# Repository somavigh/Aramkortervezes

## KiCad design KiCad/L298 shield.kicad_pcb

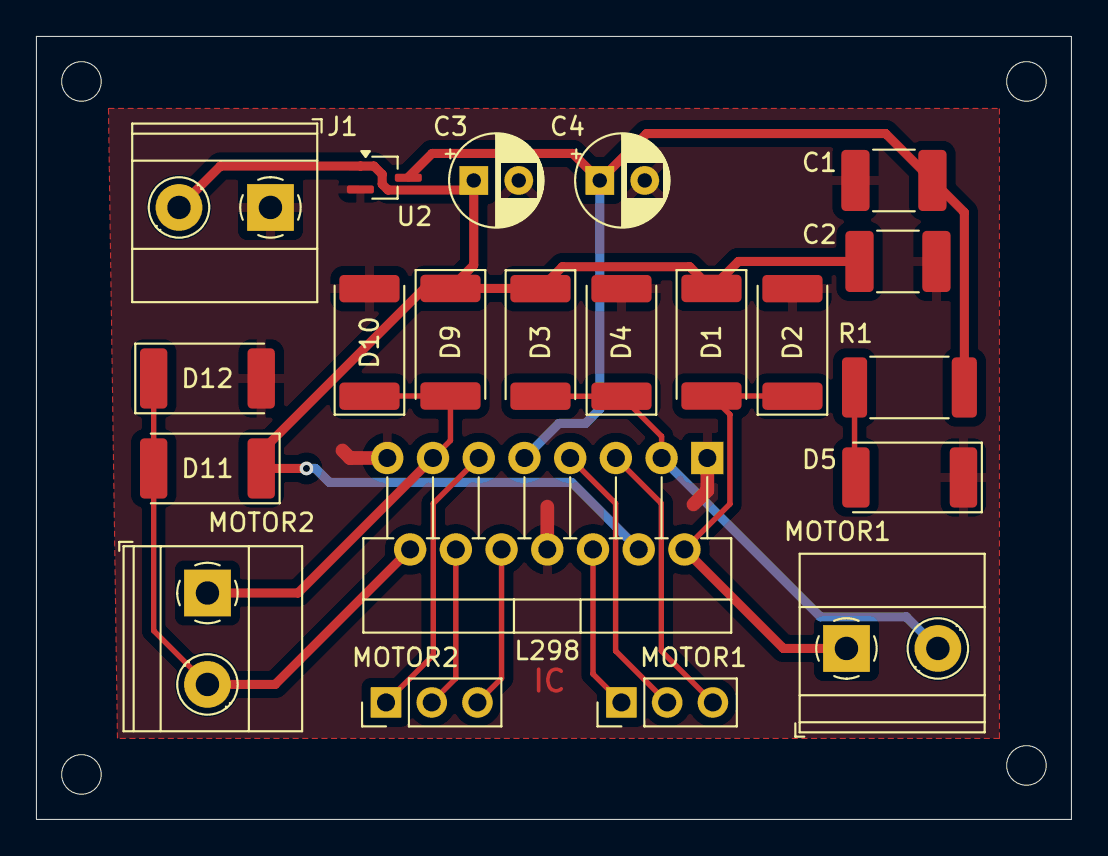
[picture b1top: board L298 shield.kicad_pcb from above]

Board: 2 copper layers, 57.5 x 43.5 mm, 21 parts (0 on the bottom side), 14 nets.

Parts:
C1, C2: 100nF; C_1812_4532Metric_Pad1.57x3.40mm_HandSolder
C3, C4: 47u; CP_Radial_D5.0mm_P2.50mm
D1, D2, D3, D4, D9, D10, D11, D12: 1N4007; D_2512_6332Metric_Pad1.52x3.35mm_HandSolder
D5: LED; LED_2512_6332Metric_Pad1.52x3.35mm_HandSolder
J1: POWER; TerminalBlock_Phoenix_MKDS-1,5-2-5.08_1x02_P5.08mm_Horizont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
L298: L298N; TO-220-15_P2.54x2.54mm_StaggerOdd_Lead4.58mm_Vertical
MOTOR1: MOTOR1 IN; PinHeader_1x03_P2.54mm_Vertical
MOTOR1#2: MOTOR1 OUT; TerminalBlock_Phoenix_MKDS-1,5-2-5.08_1x02_P5.08mm_Horizont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
MOTOR2: MOTOR2 IN; PinHeader_1x03_P2.54mm_Vertical
MOTOR2#2: MOTOR2 OUT; TerminalBlock_Phoenix_MKDS-1,5-2-5.08_1x02_P5.08mm_Horizont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
R1: R; R_2512_6332Metric_Pad1.40x3.35mm_HandSolder
U2: L7805; SOT-323_SC-70_Handsoldering

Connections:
+5V: C1.2, C4.1, L298.9 (Vss), R1.1, U2.3 (OUT)
+12V: C2.1, C3.1, D1.1 (K), D3.1 (K), D9.1 (K), D11.1 (K), J1.2, L298.4 (Vs), U2.1 (IN)
GND: C1.1, C2.2, C3.2, C4.2, D2.2 (A), D4.2 (A), D5.1 (K), D10.2 (A), D12.2 (A), J1.1, L298.1 (SENSE_A), L298.8 (GND), L298.15 (SENSE_B), U2.2 (GND)
unnamed: D1.2 (A), D2.1 (K), L298.2 (OUT1), MOTOR1#2.1
unnamed: D3.2 (A), D4.1 (K), L298.3 (OUT2), MOTOR1#2.2
unnamed: D5.2 (A), R1.2
unnamed: D9.2 (A), D10.1 (K), L298.13 (OUT3), MOTOR2#2.1
unnamed: D11.2 (A), D12.1 (K), L298.14 (OUT4), MOTOR2#2.2
unnamed: L298.6 (EnA), MOTOR1.1
unnamed: L298.7 (IN2), MOTOR1.2
unnamed: L298.5 (IN1), MOTOR1.3
unnamed: L298.11 (EnB), MOTOR2.1
unnamed: L298.12 (IN4), MOTOR2.2
unnamed: L298.10 (IN3), MOTOR2.3
